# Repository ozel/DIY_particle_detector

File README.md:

*Corresponding scientific article:* 

*Repository archive on Zenodo:* 

# DIY Particle Detector

**Short summary video on twitter**<br>
:point_right: https://twitter.com/CERN/status/1260600298206302210

A mobile low-cost spectrometer for measuring ionising radiation like alpha particles and electrons (energy range: 33 keV to 8 MeV).   
It's an experimental educational tool and citizen science device made for exploring natural and synthetic sources of radioactivity such as stones, airborne radon, potassium-rich salt or food and every-day objects (Uranium glass, ceramics, old Radium watches etc.).

<u>*The main project documentation can be found in **[the Wiki](https://github.com/ozel/DIY_particle_detector/wiki)**.*</u>   

A summary of the main aspects can be found below.    
The hardware design and documentation is licenced under the [CERN Open Hardware License](https://github.com/ozel/DIY_particle_detector/blob/master/hardware/V1.2/CERN_OPEN_HARDWARE_LICENSE_OHL_v_1_2.txt).   
The open source software is provided under the terms of the [BSD licence](https://github.com/ozel/DIY_particle_detector/blob/master/LICENSE).

This project received funding and support by [CERN](http://home.cern) and the [Fellow FreiesWissen program](https://github.com/ozel/DIY_particle_detector/wiki/Fellow-FreiesWissen-Project).

 &#8195;    

***Project Overview:***
* [How does it work?](#how-does-it-work)
* [Hardware](#hardware)
    * [Two variants](#detector-variants): Electron-Detector (easier, lower costs) and Alpha-Spectrometer (more advanced)
    * [General requirements](#general-requirements)
    * [Detector signals](#detector-signals)
* [Software](#software) for recording and analysing measurements
* [Reference measurements and plots](#reference-measurements-and-plots)
* [Workshops](#workshops) with high-school students, teachers and makers

*Much more detailed information is available in **[the project Wiki](https://github.com/ozel/DIY_particle_detector/wiki)**.*     

## How does it work?
Tiny amounts of electrical charge are generated in repurposed photodiodes by impinging particles. The charges form currents which are amplified and converted into voltage pulses that are compatible with audio/microphone signal inputs.
The size of the pulse is proportional to the energy deposited by the ionising radiation. A reference calibration with sources of known energy spectra is provided.

<br><br>

A superposition of several recorded pulse waveforms from electrons of beta decays (KCl salt sample, more info below) is shown on the right. This is the raw analog ouput signal of the detector.

Black lines in the upper area represent electronic noise, detected signal pulses from the natural radioactivity of potassium (isotope K-40) are highlighted in red.

<br>

<br>

<br>

The energy spectrum on the right - derived from the size of signal pulses - was taken from an old ceramics pendant of the Majolika manufacture (Karlsruhe/Germany) - without vacuum pump, in normal ambient air! 

The characteristic alpha energies of the uranium isotopes are about 1 MeV lower than the actual values due to internal absorption caused by the transparent surface coating on top of the orange uranium-based glaze. More details on the energy calibration below and in the [paper](https://doi.org/10.3390/s19194264).

<br>

<br>

## Hardware

More photos of finished builds from users around the world can be found in the [picture gallery](https://github.com/ozel/DIY_particle_detector/wiki/Gallery).     
The open hardware design in this repository is released under the terms of the CERN Open Hardware Licence V1.2.
Usage guidelines and legal requirements for users of this license can be found [here](https://ohwr.org/project/cernohl/wikis/Documents/CERN-OHL-version-1.2).
### Detector Variants
The same circuit board is used with two partially different sets of components in two assembly variants.
For electronic beginners, starting with the electron-detector version is *highly recommended* over the alpha-spectrometer.

* ***Alpha-spectrometer*** measuring energies of alpha particles and electrons using one BPX61 diode.<br/>
  <br/>
  After the glass window of the diode is carefully broken-up and removed, it can sense alpha particles (see close-up pictures in the [wiki](https://github.com/ozel/DIY_particle_detector/wiki/Diodes#preparation-of-the-bpx61-diode-for-alpha-spectroscopy). 
  The circuit works most precise with only one BPX61 diode (lowest electronic noise) and was specificaly tuned for this scenario.
  * [get alpha-spectrometer parts & circuit board via kitspace](https://kitspace.org/boards/github.com/ozel/diy_particle_detector/diy%20alpha%20spectrometer/)
  * [short parts overview & assembly guide for the alpha-spectrometer](https://raw.githubusercontent.com/ozel/DIY_particle_detector/master/hardware/V1.2/documentation/DIY%20detector%20-%20parts%20overview%20v1-2%20alphaspectrometer%20version.pdf)
  * [detailed assembly instructions and list of required tools](https://github.com/ozel/DIY_particle_detector/wiki/Assembly-Instructions)
  * [scientific article incl. reference energy calibration with alpha sources](https://doi.org/10.3390/s19194264)

* ***Electron/beta radiation detector*** measuring mostly electrons (plus few gamma photons) with four very low-cost BPW34F or BPW34FA diodes (<1 EUR each).<br/>
  <br/>
  This variant is not able to detect alpha particles but is  easier to operate (less sensitive to visible light and electromagnetic interference, see section on general requirements below). It is also more sensitive towards sources of low intensity (low rate of radioactive decays) since it has four times the sensor volume compared to using only one diode as sensor. This version is ideal for beginners, in total only 8 components are different compared to the alpha-spectrometer variant above. This variant is similar to the previous circuit version 1.1.
  * [get electron-detector parts & circuit board via kitspace](https://kitspace.org/boards/github.com/ozel/diy_particle_detector/diy%20electron%20detector/)
  * [short parts overview & assembly guide for the electron-detector](https://raw.githubusercontent.com/ozel/DIY_particle_detector/master/hardware/V1.2/documentation/DIY%20detector%20-%20parts%20overview%20v1-2%20electron%20version.pdf) 
  * [detailed assembly instructions and list of required tools](https://github.com/ozel/DIY_particle_detector/wiki/Assembly-Instructions)

Both kinds of diodes, the BPW34 series in various plastic cases and the BPX61 with metal casing, have the same sensitive area (~7 mm^2). The physics of these sensors when used with ionizing radiation is explained in detail in the [article corresponding to this repository](https://doi.org/10.3390/s19194264). The section about figure 1 discusses why their efficiency for detecting gamma photons is quite low in general.  

Mircoscope image of the Osram BPX61 diode on the left, the green scale indicates 2 mm. The sensitive area of the silicon chip is 2.65 x 2.65 mm^2. A bond wire from the anode pin on the right connects the top of the silicon chip (this side is also marked with a notch in the metal case, lower right corner). For detecting alpha particles, the glass window of this diode must be removed.    
Further instructions in the [wiki](https://github.com/ozel/DIY_particle_detector/wiki/Diodes).

<br>

<br><br>

<br><br>

### General Requirements

* An absolutely light-tight and electromagnetically shielding metal case is mandatory. Either a commercial one made of die casted aluminium (thick metal provides better immunity towards vibrations and prevents "microphonic effects") or an upcycled tin box for candies. Detailed recommendations in the [wiki](https://github.com/ozel/DIY_particle_detector/wiki/Enclosures).
* 9 V [battery](https://github.com/ozel/DIY_particle_detector/wiki/Batteries). NIMH-type accumulators with a nominal value of 9.6 V work best (mains-connected power supplies would introduce too much noise, always use batteries if building the detector for the first time!)
* Signal output is in the range of +/- 0.1 V and compatible with an audio/microphone input such as a [headset connector](https://github.com/ozel/DIY_particle_detector/wiki/Cables#connection-with-a-headset-socket) of a mobile phone or laptop (or an oscilloscope if available)
* The alpha-spectrometer should be operated using a low-cost USB soundcard for best results, see the [wiki](https://github.com/ozel/DIY_particle_detector/wiki/Soundcards).
* The connection cable should be shielded and not too long, recommendations in the [wiki](https://github.com/ozel/DIY_particle_detector/wiki/Cables). 

### Detector Signals
Typical signals from the electron-detector (left/top) and alpha-spectrometer (right/bottom) on an oscilloscope:
      
More details in the [wiki](https://github.com/ozel/DIY_particle_detector/wiki/Oscilloscope-Measurements).

## Software
The open source software in this repository is provided under the terms of the BSD Licence.

It consists of two parts (links to the wiki):
* [Recording, real-time display and counting of particle pulses](https://github.com/ozel/DIY_particle_detector/wiki/Software#signal-display--pulse-counting)     
  Different softwares for desktop computers as well as mobile devices are decsribed in the wiki.     
  Most universal is a [web browser application](https://ozel.github.io/DIY_particle_detector/data_recording_software/webGui/) based on the Web Audio API available in modern browsers (recent Chrome and Firefox versions work best):     
        
  This acts essentially as a software oscilloscope with trigger functionality (red line = trigger level) reading small detector pulses directly from the microphone input or headset socket of a computer or mobile device.

* [Data analysis of alpha-spectrometer measurements](https://github.com/ozel/DIY_particle_detector/wiki/Software#energy-spectra-from-alpha-particles), providing calibrated energy spectra and time series histograms

## Reference measurements and plots

Several reference measurements have been taken and stored in [data_analysis_and_reference_measurements/diode_detector/data](https://github.com/ozel/DIY_particle_detector/tree/master/data_analysis_and_reference_measurements/diode_detector/data). All have been recorded using the very low-cost [CM108 USB soundcard](https://github.com/ozel/DIY_particle_detector/wiki/Soundcards), sampling the input signal @ 48 kHz and 16-bit resolution.     
*If this whole respoitory is cloned using git, the [git LFS](https://help.github.com/en/articles/duplicating-a-repository#mirroring-a-repository-that-contains-git-large-file-storage-objects) extension must be used to get as well the large data files (~ 1 GB).*
Alternatively, the data files can be downloaded from this [Zenodo data archive](https://doi.org/10.5281/zenodo.3361764).

Overview on reference measurements:

* A mixed alpha source featuring Gd-148, Pu-239, Am-241 & Cm-244 with a combined alpha energy spectrum of 3 to 6 MeV
* 10 g of KCl (potassium chlorid) salt (an alternative to NaCl table salt) as an example for detection of electrons from beta-decays (from naturally occuring K-40)
* a small columbite stone (containing trace amounts of uranium ore), a combined source of electrons and alphas (and gamma photons which do not interact enough within the thin diode detector to be relevant)
* a watch hand from an old watch that was painted with luminescent radium paint. Featuring Ra-226 and all it's radioactive progeny isotopes

## Workshops

These DIY particle detectors have been built by high school students (age 16 - 18), teachers, makers, and citizen science enthusiasts (age ~20 - 60) during several workshops.
After a little introduction into the soldering of electronic components, the whole device can be built in less than two hours - including the modification of a candy tin box as its case.

* [S'Cool LAB Summer Camp 2017](https://indico.cern.ch/event/570855/timetable/) at CERN, [poster presentation](https://indico.cern.ch/event/570855/contributions/2616929/attachments/1504724/2344411/RG3_DIY_Detector.pdf)
* [Student Summer School of Barcelona Technoweek 2017](http://icc.ub.edu/congress/TechnoWeek2018/outreach_EN.php), [CERN news](https://home.cern/news/news/knowledge-sharing/summer-school-secondary-students-spain)
* [S'Cool LAB Summer Camp 2018](https://indico.cern.ch/event/726779/timetable/) at CERN, [poster presentation, page 3](https://indico.cern.ch/event/726779/contributions/2991390/attachments/1697186/2732121/pdfjoiner.pdf)
* [Gathering of Open Science Hardware 2018 in Shenzhen China](http://openhardware.science/gatherings/gosh-2018-2/), [workshop documentation](https://forum.openhardware.science/t/day-3-build-your-own-particle-detector-discover-natural-radioactivity/1468)

*Notes and announcements of future workshops can be found in the **[Wiki](https://github.com/ozel/DIY_particle_detector/wiki)**.*     

---

The [Pixel Detector](https://github.com/ozel/DIY_particle_detector/wiki/Pixel-Detectors) and [Diode Characterisation](https://github.com/ozel/DIY_particle_detector/wiki/Diode-Characterisation) sections have been moved to the [wiki](https://github.com/ozel/DIY_particle_detector/wiki) of this project. Both are related to the [scientific article](https://www.mdpi.com/1424-8220/19/19/4264/htm) and represent supplementary material.

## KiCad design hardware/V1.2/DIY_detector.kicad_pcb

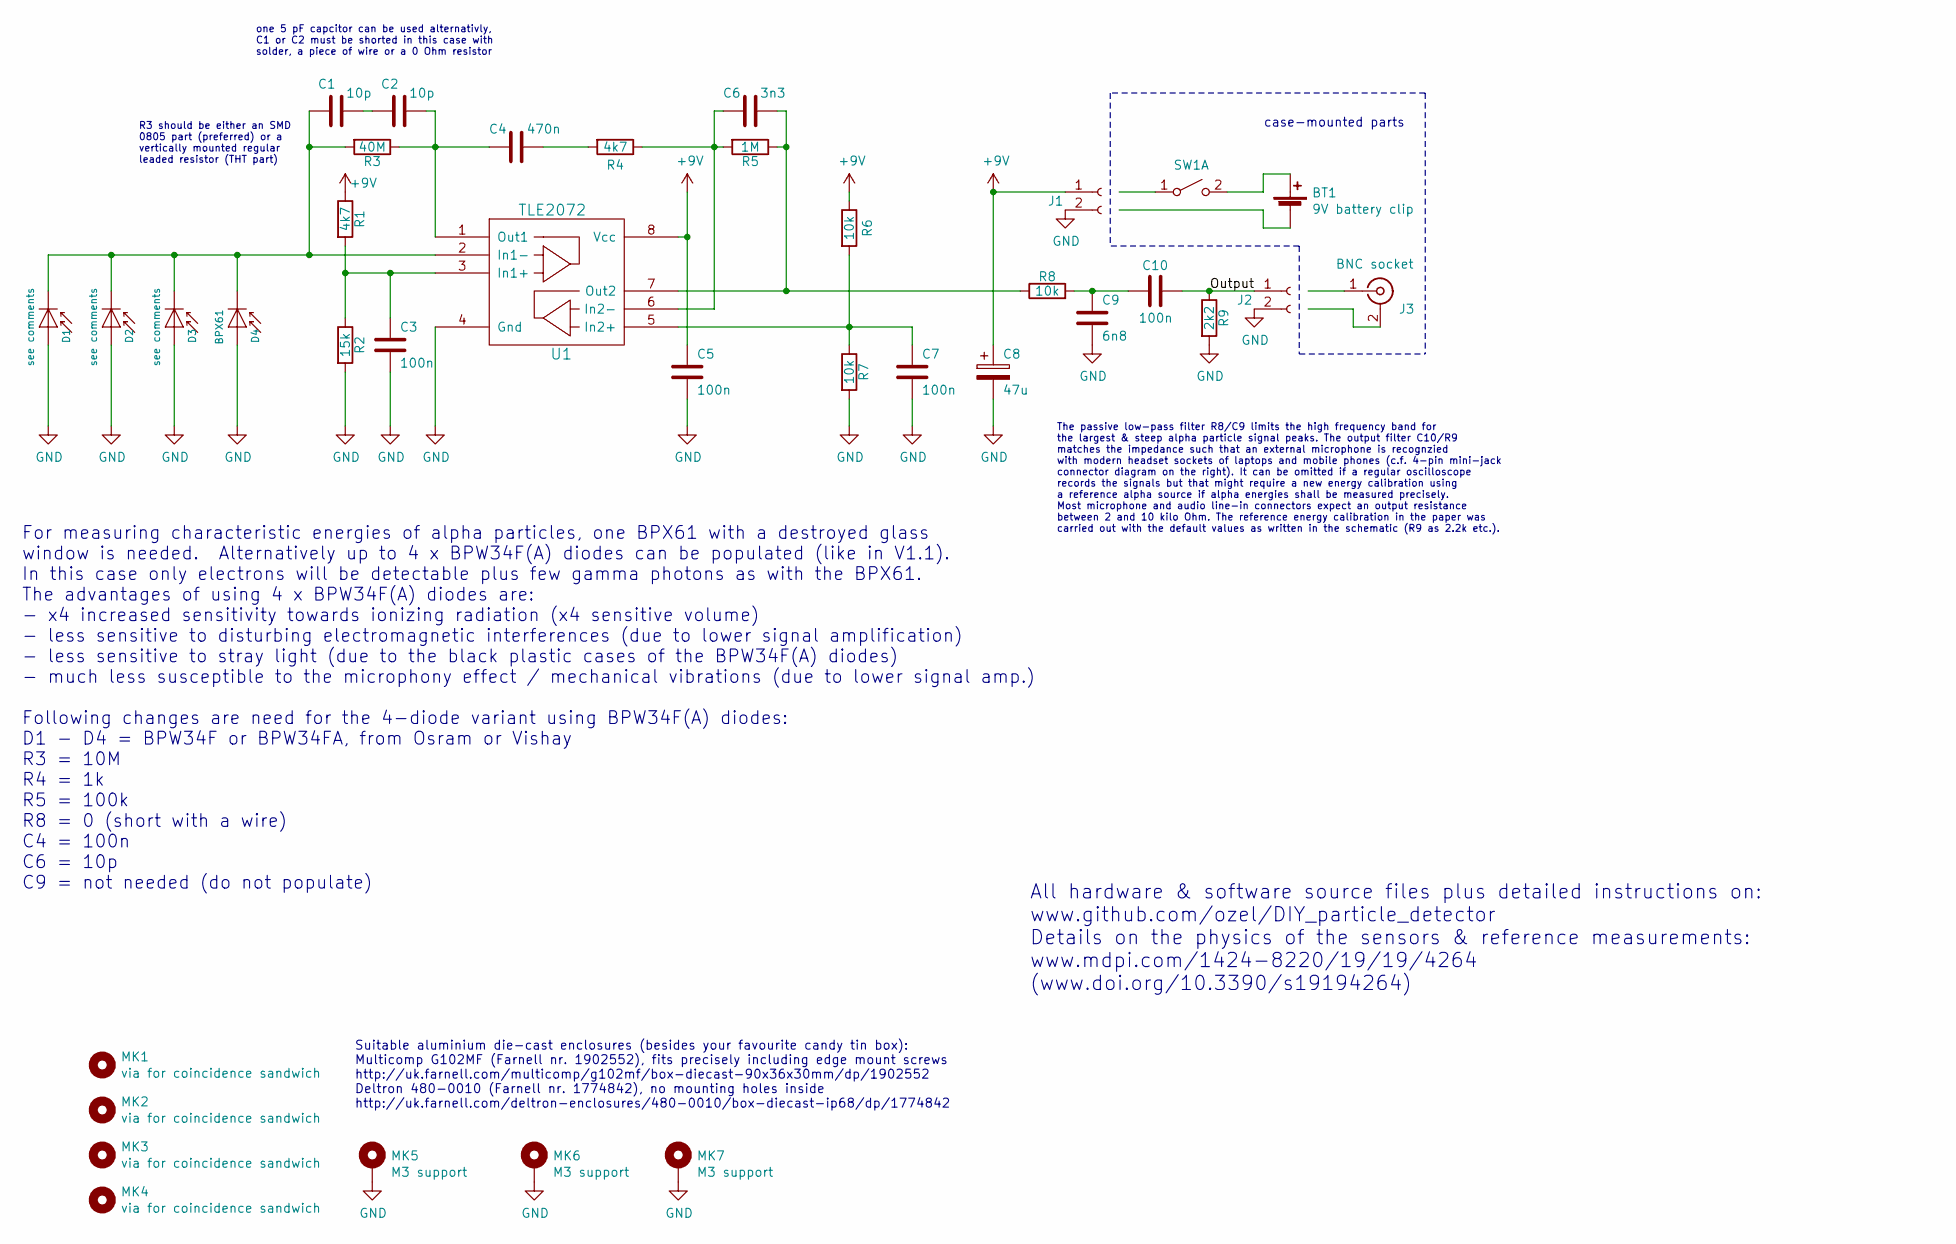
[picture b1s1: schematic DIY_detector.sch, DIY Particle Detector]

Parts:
BT1: 9V battery clip; MFG_PN FC6830; FARNELL 2817539
C1, C2: 10p; C_Disc_D3.0mm_W1.6mm_P2.50mm; MFG_PN MC0805N100J101A2.54MM; FARNELL 1694175
C3, C5, C7, C10: 100n; C_Disc_D3.0mm_W1.6mm_P2.50mm; MFG_PN MC0805Y104M500A2.54MM; FARNELL 2112751
C4: 470n; C_Disc_D3.0mm_W1.6mm_P2.50mm; MFG_PN C320C474M5U5TA; FARNELL 1457660
C6: 3n3; C_Disc_D3.0mm_W1.6mm_P2.50mm; MFG_PN TS170R1H332KSBBA0R; FARNELL 2901293
C8: 47u; CP_Radial_D6.3mm_P2.50mm; MFG_PN ECA-1JHG470; FARNELL 9693033
C9: 6n8; C_Disc_D3.0mm_W1.6mm_P2.50mm; MFG_PN TS170R1H682KSBBA0R; FARNELL 2901297
D1, D2, D3: see comments; PhotoDiode_DIL2_4.3x4.65_RM5.08; MFG_PN BPW34F/FA; FARNELL 2981621
D4: BPX61; PhotoDiode_DIL2_4.3x4.65_RM5.08; MFG_PN BPX61; FARNELL 2981630
J1, J2: Conn_01x02_Female; Pin_Header_Straight_1x02_Pitch2.54mm
J3: BNC socket; MFG_PN 13-25; FARNELL 1169699
MK1, MK2, MK3, MK4: via for coincidence sandwich; SolderWirePad_single_0-8mmDrill
MK5, MK6, MK7: M3 support; MountingHole_3.2mm_M3_ISO7380_Pad
R1, R4: 4k7; R_Axial_DIN0207_L6.3mm_D2.5mm_P7.62mm_Horizontal; MFG_PN MCMF006FF4701A50; FARNELL 2401772
R2: 15k; R_Axial_DIN0207_L6.3mm_D2.5mm_P7.62mm_Horizontal; MFG_PN MCMF006FF1502A50; FARNELL 2401785
R3: 40M; R_Axial_DIN0204_L3.6mm_D1.6mm_P2.54mm_Vertical; MFG_PN RH73H2A40MKTN; FARNELL 1174521
R5: 1M; R_Axial_DIN0207_L6.3mm_D2.5mm_P7.62mm_Horizontal; MFG_PN MCMF006FF1004A50; FARNELL 2401807
R6, R7, R8: 10k; R_Axial_DIN0207_L6.3mm_D2.5mm_P10.16mm_Horizontal; MFG_PN MCMF006FF1002A50; FARNELL 2401780
R9: 2k2; R_Axial_DIN0207_L6.3mm_D2.5mm_P10.16mm_Horizontal; MFG_PN MCMF006FF2201A50; FARNELL 2401780
SW1: -; MFG_PN 1MS1T1B1M1QE; FARNELL 9473416
U1: TLE2072; DIP-8_W7.62mm_LongPads; MFG_PN TLE2072ACP; FARNELL 3117956

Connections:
+9V: C5.1, C8.1, J1.1, R1.1, R6.1, U1.8 (Vcc)
/Output: C10.2, J2.1, R9.1
GND: C3.2, C5.2, C7.2, C8.2, C9.2, D1.2 (A), D2.2 (A), D3.2 (A), D4.2 (A), J1.2, J2.2, MK5.1, MK6.1, MK7.1, R2.2, R7.2, R9.2, U1.4 (Gnd)
unnamed: BT1.1 (+), SW1.2 (B)
unnamed: C1.1, D1.1 (K), D2.1 (K), D3.1 (K), D4.1 (K), R3.2, U1.2 (In1-)
unnamed: C1.2, C2.1
unnamed: C2.2, C4.1, R3.1, U1.1 (Out1)
unnamed: C3.1, R1.2, R2.1, U1.3 (In1+)
unnamed: C4.2, R4.2
unnamed: C6.1, R4.1, R5.2, U1.6 (In2-)
unnamed: C6.2, R5.1, R8.1, U1.7 (Out2)
unnamed: C7.1, R6.2, R7.1, U1.5 (In2+)
unnamed: C9.1, C10.1, R8.2

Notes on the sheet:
one 5 pF capcitor can be used alternativly, C1 or C2 must be shorted in this case with solder, a piece of wire or a 0 Ohm resistor
Suitable aluminium die-cast enclosures (besides your favourite candy tin box): Multicomp G102MF (Farnell nr. 1902552), fits precisely including edge mount screws http://uk.farnell.com/multicomp/g102mf/box-diecast-90x36x30mm/dp/1902552 Deltron 480-0010 (Farnell nr. 1774842), no mounting holes inside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
For measuring characteristic energies of alpha particles, one BPX61 with a destroyed glass window is needed. Alternatively up to 4 x BPW34F(A) diodes can be populated (like in V1.1). In this case only electrons will be detectable plus few gamma photons as with the BPX61. The advantages of using 4 x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
The passive low-pass filter R8/C9 limits the high frequency band for the largest & steep alpha particle signal peaks. The output filter C10/R9 matches the impedance such that an external microphone is recognzied with modern headset sockets of laptops and mobile phones (c.f. 4-pin mini-jack connecto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
case-mounted parts
R3 should be either an SMD 0805 part (preferred) or a vertically mounted regular leaded resistor (THT part)
All hardware & software source files plus detailed instructions on: www.github.com/ozel/DIY_particle_detector Details on the physics of the sensors & reference measurements: www.mdpi.com/1424-8220/19/19/4264 (www.doi.org/10.3390/s19194264)

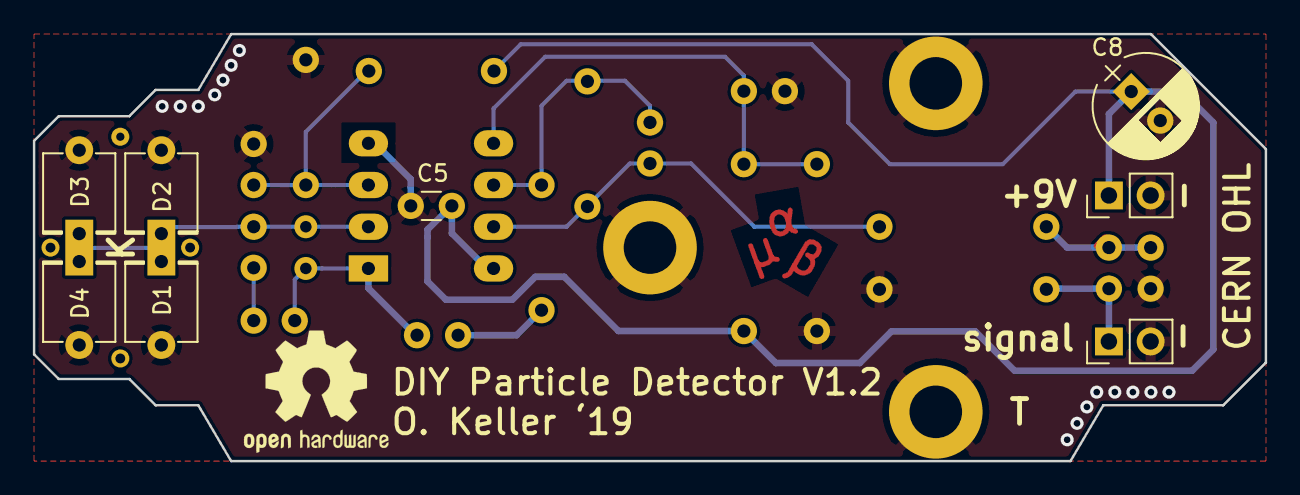
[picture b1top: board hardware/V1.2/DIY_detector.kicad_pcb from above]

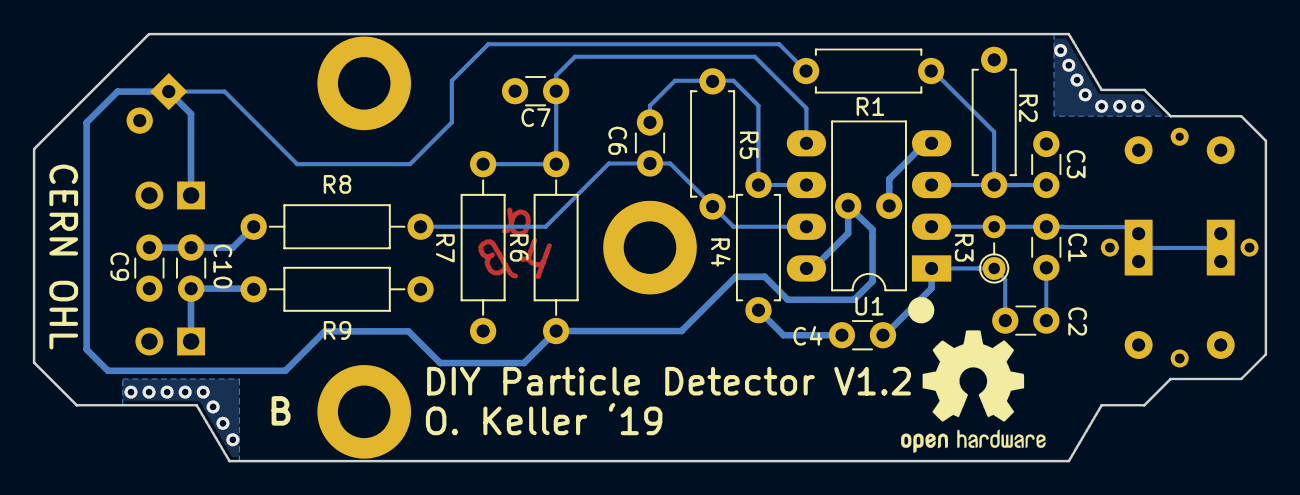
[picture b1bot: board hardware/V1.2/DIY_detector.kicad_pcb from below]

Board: 2 copper layers, 75.0 x 26.0 mm, 33 parts (18 on the bottom side), 12 nets.

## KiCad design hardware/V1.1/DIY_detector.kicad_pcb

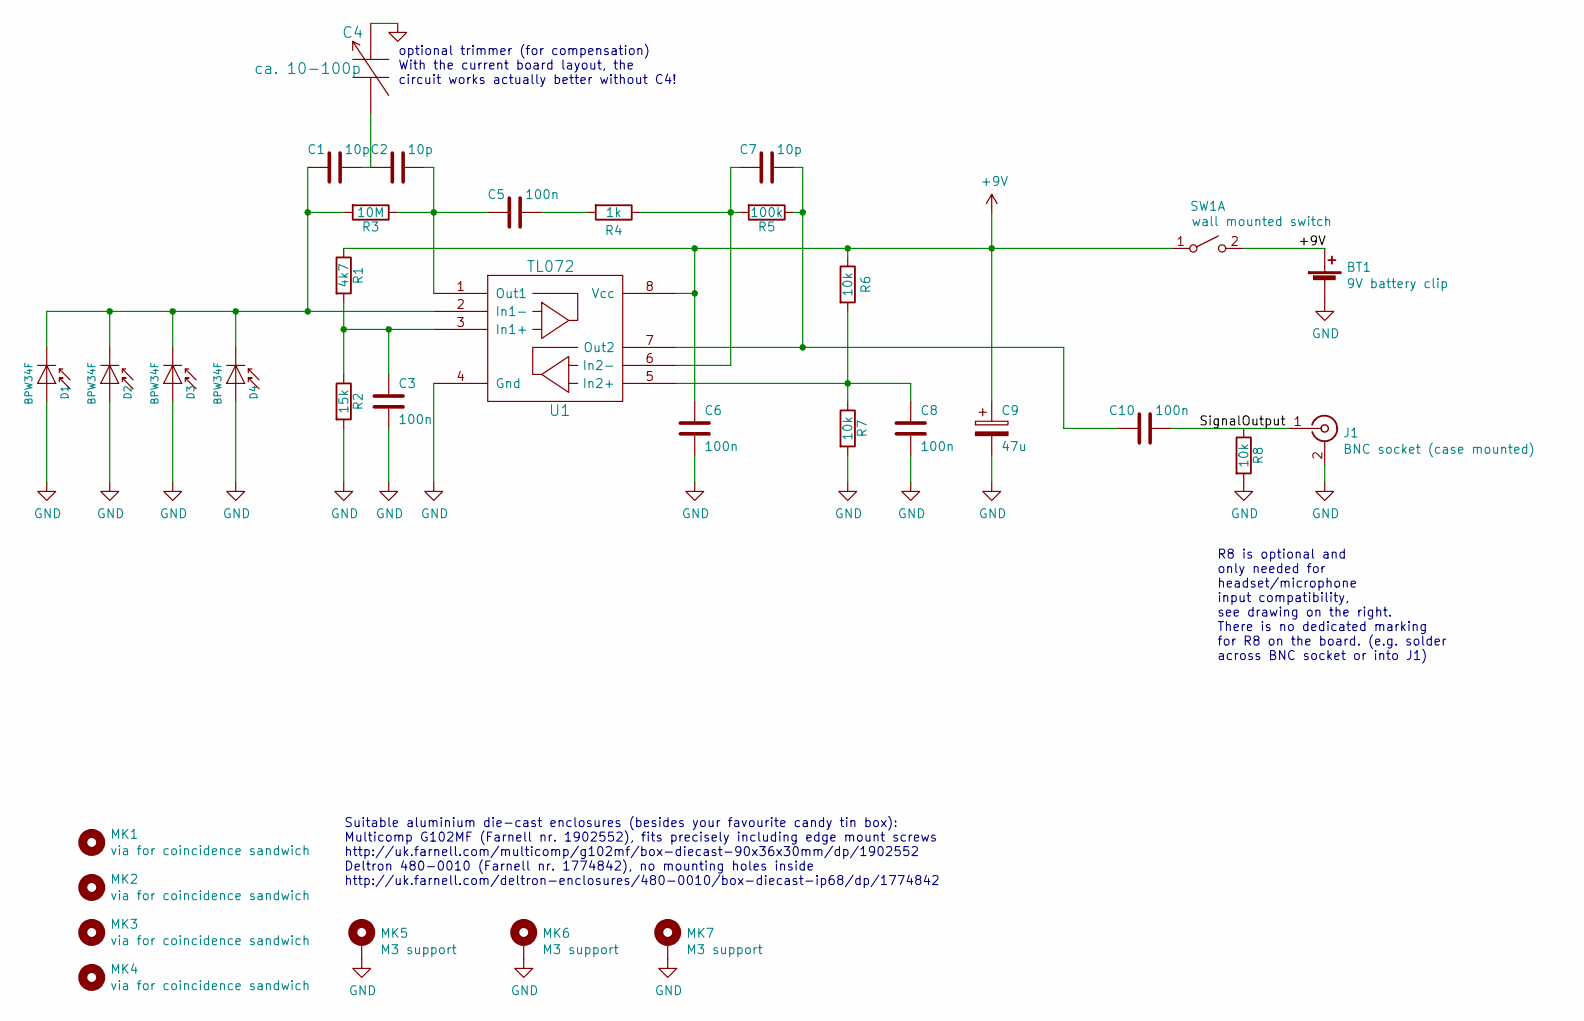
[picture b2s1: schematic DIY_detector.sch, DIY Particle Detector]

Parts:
BT1: 9V battery clip; Pin_Header_Straight_1x02_Pitch2.54mm; MFG_PN FC6830
C1, C2, C7: 10p; C_Disc_D3.0mm_W1.6mm_P2.50mm; MFG_PN MC0805N100J101A2.54MM
C3, C5, C6, C8, C10: 100n; C_Disc_D3.0mm_W1.6mm_P2.50mm; MFG_PN MC0805Y104M500A2.54MM
C4: ca. 10-100p; C_Trimmer_Murata_TZB4-B; MFG_PN TZB4P400AB10R00
C9: 47u; CP_Radial_D6.3mm_P2.50mm; MFG_PN ECA1JM470
D1, D2, D3, D4: BPW34F; PhotoDiode_DIL2_4.3x4.65_RM5.08; MFG_PN BPW34 F(A)
J1: BNC socket (case mounted); Pin_Header_Straight_1x02_Pitch2.54mm; MFG_PN 13-25
MK1, MK2, MK3, MK4: via for coincidence sandwich; SolderWirePad_single_0-8mmDrill
MK5, MK6, MK7: M3 support; MountingHole_3.2mm_M3_ISO7380_Pad
R1: 4k7; R_Axial_DIN0207_L6.3mm_D2.5mm_P7.62mm_Horizontal; MFG_PN MCMF006FF4701A50
R2: 15k; R_Axial_DIN0207_L6.3mm_D2.5mm_P7.62mm_Horizontal; MFG_PN MCMF006FF1502A50
R3: 10M; R_Axial_DIN0204_L3.6mm_D1.6mm_P2.54mm_Vertical; MFG_PN MCMF006FF1005A50
R4: 1k; R_Axial_DIN0207_L6.3mm_D2.5mm_P7.62mm_Horizontal; MFG_PN MCMF006FF1001A50
R5: 100k; R_Axial_DIN0207_L6.3mm_D2.5mm_P7.62mm_Horizontal; MFG_PN MCMF006FF1003A50
R6, R7, R8: 10k; R_Axial_DIN0207_L6.3mm_D2.5mm_P10.16mm_Horizontal; MFG_PN MCMF006FF1002A50
SW1: wall mounted switch; MFG_PN 1MS1T1B1M1QE
U1: TL072; DIP-8_W7.62mm_LongPads; MFG_PN TL072ACP

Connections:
+9V: BT1.1 (+), C6.1, C9.1, R1.1, R6.1, SW1.1 (A), SW1.2 (B), U1.8 (Vcc)
/Output: C10.2, J1.1 (In)
GND: BT1.2 (-), C3.2, C4.2, C6.2, C8.2, C9.2, D1.2 (A), D2.2 (A), D3.2 (A), D4.2 (A), J1.2 (Ext), MK5.1, MK6.1, MK7.1, R2.2, R7.2, R8.2, U1.4 (Gnd)
unnamed: C1.1, D1.1 (K), D2.1 (K), D3.1 (K), D4.1 (K), R3.2, U1.2 (In1-)
unnamed: C1.2, C2.1, C4.1
unnamed: C2.2, C5.1, R3.1, U1.1 (Out1)
unnamed: C3.1, R1.2, R2.1, U1.3 (In1+)
unnamed: C5.2, R4.2
unnamed: C7.1, R4.1, R5.2, U1.6 (In2-)
unnamed: C8.1, R6.2, R7.1, U1.5 (In2+)
unnamed: C7.2, C10.1, R5.1, U1.7 (Out2)

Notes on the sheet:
optional trimmer (for compensation) With the current board layout, the circuit works actually better without C4!
R8 is optional and only needed for headset/microphone input compatibility, see drawing on the right. There is no dedicated marking for R8 on the board. (e.g. solder across BNC socket or into J1)
Suitable aluminium die-cast enclosures (besides your favourite candy tin box): Multicomp G102MF (Farnell nr. 1902552), fits precisely including edge mount screws http://uk.farnell.com/multicomp/g102mf/box-diecast-90x36x30mm/dp/1902552 Deltron 480-0010 (Farnell nr. 1774842), no mounting holes inside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

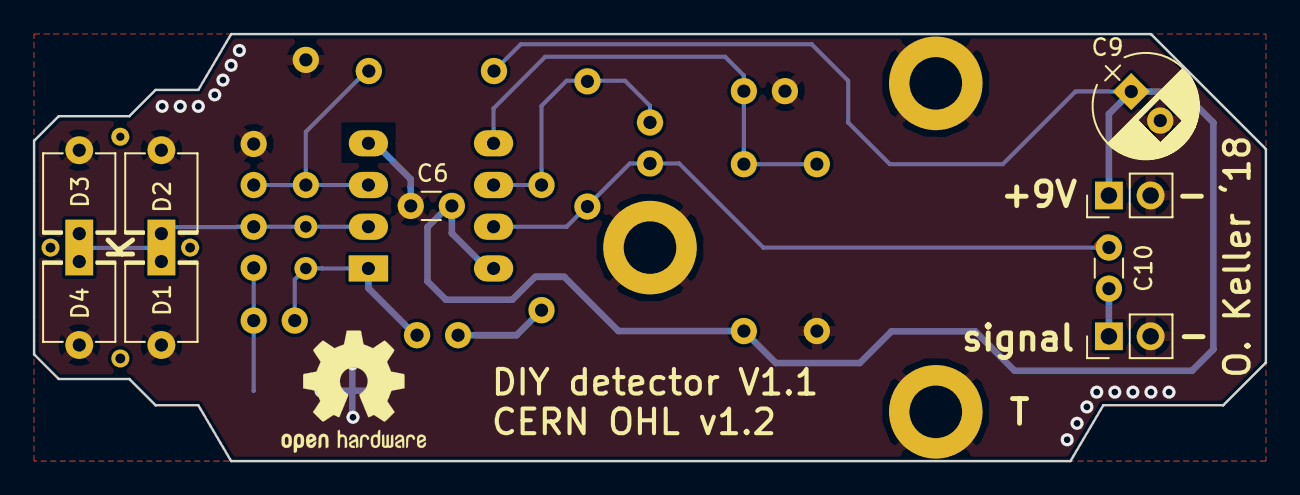
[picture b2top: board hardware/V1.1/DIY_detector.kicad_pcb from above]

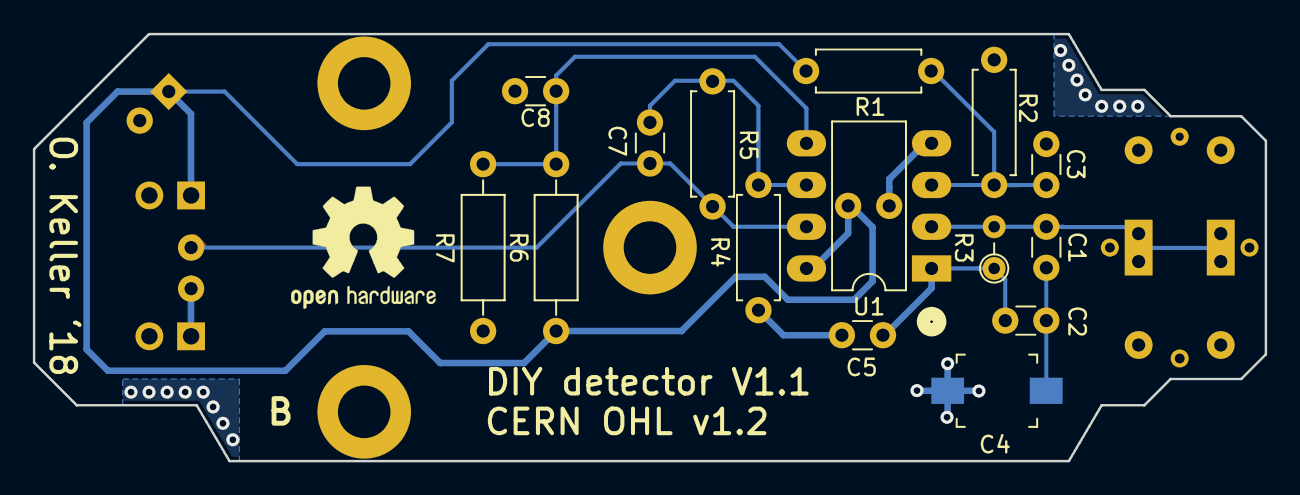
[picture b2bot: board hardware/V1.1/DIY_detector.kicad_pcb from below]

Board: 2 copper layers, 75.0 x 26.0 mm, 31 parts (15 on the bottom side), 11 nets.

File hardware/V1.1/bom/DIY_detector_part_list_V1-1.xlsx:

Reference | Value | Manufacturer | Part number | Vendor | Vendor part number | Quantity | Comment
BT1 | 9V battery clip | CLIFF | FC6830 | Farnell | 2817539 | 1
C1,C2,C7 | 10p | Multicomp | MC0805N100J101A2.54MM | Farnell | 1694175 | 3
C4 | ca. 10-100p | Murata | TZB4P400AB10R00 | Farnell | 1760637 | 1 | optional, don't populate
C3,C5,C6,C8,C10 | 100n | Multicomp | MC0805Y104M500A2.54MM | Farnell | 2112751 | 5
C9 | 47u | Panasonic | ECA1JM470 | Farnell | 9693858 | 1
D1-D4 | BPW34F | Osram/Vishay | BPW34 F(A) | Farnell | 1212740 | 4
J1 | BNC socket (case mounted) | Multicomp | 13-25 | Farnell | 1169699 | 1
R1 | 4k7 | Multicomp | MCMF006FF4701A50 | Farnell | 2401772 | 1
R2 | 15k | Multicomp | MCMF006FF1502A50 | Farnell | 2401785 | 1
R3 | 10M | Multicomp | MCMF006FF1005A50 | Farnell | 2401834 | 1
R4 | 1k | Multicomp | MCMF006FF1001A50 | Farnell | 2401753 | 1
R5 | 100k | Multicomp | MCMF006FF1003A50 | Farnell | 2401807 | 1
R6-R8 | 10k | Multicomp | MCMF006FF1002A50 | Farnell | 2401780 | 3
SW1 | wall mounted switch | Multicomp | 1MS1T1B1M1QE | Farnell | 9473416 | 1
U1 | TL072 | TI | TL072ACP | Farnell | 1103005 | 1

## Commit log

2019-08-05 Create LICENSE
    concerning all software files in this repository (python, HTML/javascript etc.)
2019-08-05 Initial commit Includes HW versions V1.1 and V1.2, released here under the CERN OHL License V 1.2 All software sources released here under the BSD License
2019-08-06 update BPX61 orientation in renderings
2019-08-06 smaller image crops
2019-08-06 microscope image of Osram BPX61 diode, with glass window
2019-08-06 updating schematic PDF
2019-08-06 Initial README
    Readme pulling everything together in an overview, pointing out the structure and individual folders of this repo
2019-08-06 fixing typos and links
2019-08-06 hardware pictures smaller
2019-08-06 fixing image layout
2019-08-06 moving image description up
2019-08-06 correcting file name
2019-08-07 adding gerber files
2019-08-09 optimising threshold for V1.1
2019-08-12 adding debug field showing*mediaDevice info for now
2019-08-12 adding doping profile plot
2019-12-28 adjusting font sizes and plot annotations
2019-12-29 adding improved persistence plots for waveform superposition
2019-12-29 updating parts in schematic
    U1 must be TLE2072 (like in the paper). Updated several vendor part numbers as well.
2019-12-29 embedding small artwork in front copper layer
2019-12-29 ignore spyder project folder
2019-12-29 adding green highlight marker for calibration purposes
    vertical position can be controlled via keypad in fine and coarse steps
    also improved sonification
2019-12-29 updating documentation and new parts overview sheets for assembly
    updating PDF of schematic, gerber files of board layout, and fixing some typos as well
2019-12-29 simplified description about the two variants
    adding new parts overview sheets and link to the updated schematic, referenced the article corresponding to this repo which was pusblished in the Sensors magazine
2020-01-01 BOM files in preparation for Kitspace release
2020-01-02 improving kitspace files
2020-01-02 kitspace linking test
2020-01-17 renderings and 3D part models for both variants
    including generated 3D models for all THT resistors, opamp chip model
    with label. also created more accurate BPX61 TO-39 model.
    Schematic and exported .xml BOM file have two new columns which store
    part values and 3D model locations of the electron detector assembly
    variant (VALUE_B, 3D_B)
2020-01-17 cropped renderings, added BPX61 detail
2020-01-17 bottom rendering crops and file typo fix
2020-01-17 pictures of alpha spectrometer built into candy box
2020-01-17 include new candy box pictures in readme
2020-01-17 adjusting img sizes
2020-01-18 removing picture for now
2020-01-18 absolute link
2020-01-18 adding kitspace links
2020-01-18 removed site links
2020-01-18 improved text layout
2020-01-21 BPX61 diode model without window
    improved parts overview pdf, added example oscilloscope plots of KCL
    (betas/gammas only) for both detector variants
2020-01-22 adding annotation to oscilloscope plots
2020-01-22 including oscilloscope plots with annotations
2020-01-22 typo in anchor link
2020-02-12 fixing Alpha-spectro kitspace bom
    removed D1-D3 which are not required in this version and add switch part
    reference of all four suppliers
2020-02-12 updated electron-detector bom
    better reference for the BPW34 FA diode at Farnell with improved
    availability
2020-02-12 better refs for Digikey BOMs
2020-02-15 smaller renderings
    for kitspace readmes
2020-02-15 improving kitspace
    included small renderings and sub-project identifiers without spaces
2020-05-14 adding CERN tweet
2020-05-15 add Majolika ceramics alpha spectrum
2020-05-15 added alpha spectrum
2020-05-15 add hw overview image
2020-05-15 rearranged header layout
2020-05-26 ignore BOM folders
    this will hopefully tag the repo correctly as python based
2020-06-02 more images for the wiki
2020-06-02 major restructuring of readme
    uncluttered and moved many details over to the Github wiki
    added table of contents overview
2020-06-02 typo and layout ifx
2020-06-02 layout fix
2020-06-02 fix links
2020-06-21 picture of die-cast Al enclosures
2020-07-27 Seperate kitspace summaries for different variants
    Someone on twitter was confused about the descriptions
2020-10-09 adding 2nd KiCAD pcb file for Kitspace's assembly guide
    DIY_detector_electron-variant.kicad_pcb shows the alternative part
    selection (values & 3D models). It is generated from VALUE_B and 3D_B
    fields in the schematic file which is the common base for both
    .kicad_pcb files.
    This new pcb design file is only for kitspace's assembly guide feature
    (interactive BOM).
2020-10-09 updating part visibility
    set several footprints as virtual to prevent appearance in the
    interactive assembly guide
2020-10-09 major readme update
    updated and added many links to the wiki. removed less relevant parts which are now more detailed on the wiki
2020-10-09 direct PDF links
2020-11-04 updating BOMs fxing part number for R5@Farnell and some house keeping
2020-11-24 extended electron-detector handout PDF
2020-11-29 add German version, minor improvements in the english one
2020-12-02 extended webGUI with two modes for recording electrons and alphas
2020-12-26 fix: small errors
2021-06-17 added support info and link to fellow project page
2021-06-18 fixed typo

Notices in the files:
hardware/V1.1/DIY_detector.kicad_pcb:
CERN open hardware license V1.2
CERN OHL v1.2
hardware/V1.1/DIY_detector.sch:
CERN Open Hardware License (CERN OHL V1.2)
